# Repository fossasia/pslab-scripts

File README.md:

# PSLab

This repo is used for scripts and operators that collect data of specific sensors connected with the PSLab.

PSLab is a tiny pocket science lab that provides an array of equipment for doing science and engineering experiments. It can function like an oscilloscope, waveform generator, frequency counter, programmable voltage and current source and also as a data logger. Our website is at https://pslab.io

## The PSLab Sensor Box

For a quick start jump to the [initial setup](#initial-setup) or the [basic usage](#basic-usage) section.

In this project four different experimental setups of the [PSLab v5](https://pslab.io/wp-content/uploads/PSLab-Data-Sheet.pdf) are created, each incorporating a different sensor: one measuring [CO2](/docs/sensors.md#⬛-co2e-sensor-ccs811), one for [oxygen](/docs/sensors.md#🟦-oxygen-sensor-ao-03), one for [temperature](/docs/sensors.md#🟩-temperature-sensor-lm35), as well as one setup measuring the [light intensity in lux](/docs/sensors.md#🟨-light-intensity-sensor-gl5528).
Details for those sensor setups can be found in the [docs](/docs/sensors.md).

In addition, the following **hardware components** are connected to the PSLabs:

- A **Raspberry Pi Zero W** to store the sensor data permanently on an SD card and, at the same time, make this data available via the Raspberry Pi's WiFi module. The "Zero" is especially handy here, as it is the most lightweight Raspberry Pi version. Both, the Raspi and the PSLab are screwed on to a plexiglass panel that is slid into the box using the boxe's integrated rail system.
- A **Button** to safely shutdown the Raspberry Pi. It needs to be long pressed for at least one second in order to trigger the device's shutdown. Here, one button terminal is plugged into GPIO pin 27, while the other terminal is plugged to the ground.
- The high accuracy I²C **real time clock (RTC)** model [DS3231](https://www.analog.com/media/en/technical-documentation/data-sheets/DS3231.pdf). It contains a small battery and ensures that the device's time progresses, even if the main power source is unavailable. This RTC therefore makes timestamps in the output data possible during times, where the PSLab sensor box can not access the internet. The five pins of this Pi HAT are plugged into pins 1, 3, 5, 7 and 9 of the Raspberry Pi Zero W.
- A 3D printed, splashproof [casing](/docs/casing/README.md) with a USB c port and a lasercut shield to hold the electronics securely in place.

The following **features** are implemented on top of that:

- Each measured data point is then immediately shared via OSC as `/<item_name> <measured_value>, <unit>, <timestamp>`. Additionally it is written into the CSV file of this measurement session. The file is structured as `<timestamp>, <measured_value>, <unit>, <item_name>`.
- The devices are connected to a public WiFi Network, where they share their data as part of an IoT approach. Initially, each device opened their own WiFi Hotspot, however this was later **discontinued**, as the new requirement of accessing all devices within one common network came up.
- A [samba file sharing server](https://raspberrypi-guide.github.io/filesharing/filesharing-raspberry-pi) makes the folder "/home/foss/data" of the Raspberry Pi publicly available to all devices within the WiFi Hotspot. This also enables users to modify or delete the CSV measurement data within this folder remotely via their PC or mobile phone. The measurements are not only provided to this file sharing server in real-time, but also stored on the SD card permanently.
- The measurement it triggered automatically after startup. This is done by a custom [systemd](https://www.raspberrypi-spy.co.uk/2015/10/how-to-autorun-a-python-script-on-boot-using-systemd/) service.
- The Raspberry Pi itself is running the code from the master branch this Github repository. This makes code updates easy to distribute on all devices. All PSLab sensor boxes run the exact identical code, with the only difference being the experiment type parameter with which `init_pipe.py` is called by the systemd service.

## Accessing the Raspberry Pi

In order to modify the software, the data on the Raspberry Pi's SD card needs to be accessed.
This can either be done by plugging the SD card into a computer, accessing the Raspberry Pi via SSH, or by using the Raspi as a computer itself. In the following, the latter two methods are explained in detail.
In any case, the SD card should never be cleared fully, because this would delete the operating system and therefore stop the Raspberry Pi from working.

### Using the Raspberry Pi as an Independent Computer

Here, a monitor needs to be connected to the microHDMI slot of the Raspi. Simultaneously a mouse and a keyboard need to be linked to the inner microUSB slot via an USB hub. Make sure to perform this cabling-up before attaching the device to the electricity source.

### Accessing the Raspberry Pi via SSH

An [SSH access](https://itsfoss.com/ssh-into-raspberry/) can be more convenient, as there is no additional cabling needed.
However, to establish this connection, the Raspberry Pi needs to be in the same WiFi network as the connecting laptop. If that is not the case yet, there is no way around connecting the Raspi to a monitor first, in oder to set up this WiFi connection, as the Raspberry Pi Zero W does not have a LAN port. Also, the network specific **IP address** of the Raspberry Pi needs to be known. It can be retrieved by executing the command `ifconfig` in the Raspi's terminal while having it connected to a monitor. The IP address can then usually be found in the "wlan0" paragraph and is formatted in a "000.000.000.000" pattern.
To then establish the ssh connection, the following steps need to be executed:

1. Ensure that the PC is connected to the same WiFi Hotspot as the PSLab Sensor Box.
2. Open the SSH connection by running `ssh foss@<ip>` in the PC's terminal and entering the password `foss` when asked.
3. Now you are operating on the Raspberry Pi.

## Initial Setup

Before using the devices in an own network, a one time setup is needed.
Once this is done, for every following usage, please directly jump to the [basic usage](#basic-usage) section.

Both, the OSC messages and the CSV file, of the measurement can be retrieved via WiFi.
Currently, the devices are connected to a dummy WiFi Hotspot with the credentials `myHotspot` as the SSID and `password123` as the password.
Thus, for basic testing, one can just open a Hotspot with these details on a Phone/PC, the devices will automatically connect and the measurement data can be obtained.

However, for more extensive usage, it is obviously more convenient to connect the PSLab Sensor Boxes to the buildings usual WiFi.
For example a connection to eduroam can be established by [logging in with one's university credentials](https://www.uni-weimar.de/fileadmin/user/uni/zentrale_einrichtungen/scc/wlan/Ubuntu.pdf).
The network connection can be changed by [connecting the Raspberry Pi to a monitor](#using-the-raspberry-pi-as-an-independent-computer) and logging into the new WiFi Hotspot using the graphical user interface. Once connected, it is also possible to [set a static private IP address](https://www.tomshardware.com/how-to/static-ip-raspberry-pi) for the Raspberry Pi in this network.
This can be very useful, for example, in order to make the Raspi reliably accessible via SSH.
Please make sure that the devices can see each other in the network and disable/ reconfigure the [VLAN](https://www.techtarget.com/searchnetworking/definition/virtual-LAN), in case one is set up.

Additionally, the IP address and port of the OSC server, need to be edited according to the actual address of the OSC receiver.
This can be done by adjusting the `OSC_RECEIVER_IP` and the `OSC_RECEIVER_PORT` constants on the Raspberry Pis.
The only loophole to this, is to use a OSC server at the pre-configured IP address of `192.168.173.152`.
However, that's not always possible, depending on the available namespace of the network.

## Basic Usage

Once a power source (power bank or cord to electricity outlet) is connected to the PSLab sensor box and the device has fully booted (this **may take a minute ot two**), a new measurement is automatically started. The measurement results are now simultaneously shared via the [Open Sound Control Protocol (OSC)](https://en.wikipedia.org/wiki/Open_Sound_Control) and collected in a [CSV](https://en.wikipedia.org/wiki/Comma-separated_values) file.
To retrieve this data, please connect your own PC/Phone to the same public WiFi Hotspot, that the PSLab Sensor Box is connected to (see [initial setup](#initial-setup)).

### Accessing the CSV Measurements

The CSV measurements of each PSLab sensor box can be retrieved in real time from the file server via WiFi:

1. A detailed manual on how to connect to the devices file server for the first time can be found in the [docs](/docs/network_connection_manual.md).
2. Once connected, the PSLab will appear in the "Network Devices" section.

Access the data folder and fetch the most recent CSV measurement data file. This file can for example be opened by Excel or just a normal text editor. The current measurement file is updated automatically every few seconds, to see these real time changes, just close and reopen the file.

Analysis tasks can now be performed on these data sheets, for example by importing them into [Jupyter Notebook](https://jupyter.org/).

### Receiving the OSC Messages

The OSC messages are sent to the specified IP address upon startup. To receive those messages a OSC server like this is necessary:

```[python]
import argparse
from pythonosc.dispatcher import Dispatcher
from pythonosc import osc_server

if __name__ == "__main__":
    parser = argparse.ArgumentParser()
    parser.add_argument("--ip", default="192.168.173.152")
    parser.add_argument("--port", type=int, default=5005)
    args = parser.parse_args()

    dispatcher = Dispatcher()
    dispatcher.map("/light", print)
    dispatcher.map("/temp", print)
    dispatcher.map("/co2", print)
    dispatcher.map("/oxygen", print)

    server = osc_server.ThreadingOSCUDPServer(
        (args.ip, args.port), dispatcher)
    server.serve_forever()
```

This server uses the [python-osc](https://github.com/attwad/python-osc) package to receive and decode the messages. The package can be installed by executing `pip3 install python-osc` in the PC's terminal.
Please note that this setup only works if the IP address, specified as `OSC_RECEIVER_IP`, is identical to the IP address stated in the server scrips (in line 7 here) and corresponds to the laptops own IP address (obtainable by executing "ifconfig" in the terminal). This OSC server for example produces the following output when, at the same time, the Oxygen Sensor Box and the Light Sensor Box are sending OSC data to this IP address at port 5005:

### Example Measurement Session

When for example using the PSLab Sensor Box "Lux", changes in the environment's light intensity can be measured.
After attaching the box to a power bank and waiting for two minutes, the device starts measuring.

The running OSC server on our laptop, that is connected to the same WiFi Hotspot as the Sensor Box, then receives the following data:

```
/light 109.5234702837157 lux 21-07-2023 20:44:12
/light 108.62976013160224 lux 21-07-2023 20:44:13
/light 114.54458695414951 lux 21-07-2023 20:44:14
```

To test the sensor and observe the changes in the environment, the lights are now turned off.

This results in the following OSC messages:

```
/light 6.80740388396548 lux 21-07-2023 20:46:04
/light 7.05431189748499 lux 21-07-2023 20:46:05
/light 7.52577384043171 lux 21-07-2023 20:46:06
```

To then test the sensor at a very hight brightness, we turned the lights on again and exposed the photoresistor to a flashlight:

Thus, the OSC server receives these messages:

```
/light 1721.79974583536023 lux 21-07-2023 20:47:38
/light 1902.29013779831879 lux 21-07-2023 20:47:39
/light 1483.70672770591856 lux 21-07-2023 20:46:40
```

In an analogue way, the temperature sensor can be tested by warming it up with one's finger tips,
while the CO2 and oxygen sensors can by tested by exposing them to exhaled air.

### Ending the Session

To eventually trigger the shut down process of the Raspberry Pi, please press the attached button for one to two seconds.
After waiting 20-30 seconds, the shut down is completed, the green indication light on the Raspberry Pi goes off and the electricity source can be unplugged.
Technically, the measurement session can also be terminated by just unplugging the power source directly, however in the long term,
this technique can be harmful for the Raspberry Pi's file system.

## Debugging

As this is a hardware project, it is not unlikely that at some point in time, one of the cables or other components will cause problems. To then solve this, it is important to localize the error. Here, different levels of debugging can help, depending on the supposed location of the problem.
Basic debugging steps may be:

- Turn the Raspberry Pi off (by using the button) and on again (by plugging in a power bank).
- Make sure all cables are attached firmly. Try unplugging and reattaching them.
- Sometimes the output voltage of a laptop's USB port might vary a bit to much, try using a power bank instead.
- Make sure the lights on the PSLab are glowing. Otherwise there probably is a problem with the boxes' charging cable or the PSLab itself.
- Make sure the light on the Raspberry Pi is glowing or blinking. This indicates a successful booting of the Raspbian OS.
- Try using one PSLab Sensor Box after another, not in parallel.
- If the device does not connect to the WiFi network (for example checkable via Linux' `nmap` tool), try having the network open already during the Raspberry Pi's booting process.
- Try opening the Hotspot, that the Sensor Boxes are connected to, from another device (e.g. phone, instead of laptop).

Some more advanced debugging techniques include the following:

### Debugging Sensor Issues - On a PC

To ensure that the PSLab itself and the sensor are working properly,  the following test can be executed.
Please note that this routine is the only one that is executed on a normal (Linux)
**PC, instead of the Raspberry Pi**, in order to abstract from any Raspi specific problems.

1. Ensure that python3 is installed on your PC by running `python3 --version` in the terminal. In case there is no item found, install version 3.6 by `sudo apt-get install python3.6` and reboot your system afterwards to ensure that everything is fully loaded.
2. Install the pslab-python library on the PC by executing `pip3 install pslab`.
3. Detach the PSLab and the corresponding sensor from the Raspberry Pi by removing the
microUSB to microUSB cable between Raspi and PSLab. Instead connect the microUSB port of the PSLab to one of the PC's USB ports.
4. Download the pslab-scripts library by running `sudo git clone https://github.com/fossasia/pslab-scripts.git`.
5. Open the repository folder by executing `cd pslab-scrips`.
6. Start the execution a sensor type specific test by running `sudo python3 init_pipe.py <type>` (for example
`sudo python3 init_pipe.py oxygen`). This execution can always be stopped by hitting ctrl+c.
7. Check the fetched measurement data by accessing the file located in `/home/<user name>/data`.

### Debugging the Startup Script - On the Raspberry Pi

Often times the script itself actually works fine, but the startup manager might start it
too early, causing resource conflicts and other issues to arise.
One option to debug this, is to first make sure that the script itself works fine by running `sudo python3 /home/foss/code/init_pipe.py <type>`
on the Raspberry Pi (for example `sudo python3 init_pipe.py oxygen`) and checking the results in
`/home/foss/data`. If those results look good, but the data fetching upon startup still does not work, the error logs of the startup script can be examined by executing `journalctl -u startup.service --since yesterday` in the Raspi's terminal.

## Advanced Usage

Different software and hardware projects can be realized on this combination of PSLab and Raspberry Pi.
Some ideas for modifying the existing software are listed below.
As python3, the pslab-python library, as well as this pslab-scripts repository, are already installed on the Raspberry Pis, **no** additional installation is needed here.

### Adjusting the measurement interval

Currently a new data point is retrieved from the sensor every second. This can be changed by adjusting the value for the`MEASURING_INTERVAL`. This constant can be found in the `/home/foss/pslab-scripts/measure.py` file on the Raspberry Pi.

### Adjusting the flushing interval

The data points are flushed into the CSV file after every 10 measurements in the current implementation. To change this, the `FLUSHING_THRESHOLD` value in `/home/foss/pslab-scripts/store_data.py` can be adjusted on the Raspi.

### Accessing the continuous measurement data stream via an API

As of now, the measurement data is redirected into a CSV file and OSC messages by the pipe function. This can however be modified freely, for example by adding an additional step 
to transform and output some data into the data exporting function.
This new process can freely process the measured data points, received via `connection.recv()`.

### Fetching a software update from Github

1. Open the terminal.
2. Open the folder "pslab-scripts" by typing `cd /home/foss/pslab-scripts`.
3. Enter `git pull` in the terminal to fetch the new changes in software.

### Changing the sensor type

By adjusting the experiment type parameter in the systemd service "startup.service", the supported sensor type of this specific PSLab sensor box can be changed easily:

1. Open a terminal.
2. Type `sudo nano /lib/systemd/system/startup.service`.
3. The "startup.service" file is now opened in a simple text editor. Here, you can adjust the experiment type parameter, e.g. from "light" to "co2", in case the PSLab sensor box for light shall now be used with a CO2 sensor. Besides "light" and "co2", also "oxygen" and "temp", are supported as parameters here.
4. Save the changes by pressing ctrl+o. Exit the editor by pressing ctrl+x.
5. The changes take effect once the device is rebooted. This can for example be done by executing `sudo reboot`.

## Repository Structure

```
📦pslab-scripts
 ┣ 📂docs                               # Supplementary material
 ┃ ┣ 📂ao-03_amplifier_circuit_design  # KiCad project files of the custom circuit board for the AO-03 sensor
 ┃ ┃ ┗ 📜...
 ┃ ┣ 📂casing                          # Information about the 3d printed casing, as well as the lasercut shield
 ┃ ┃ ┣ 📜README.md
 ┃ ┃ ┗ 📜...
 ┃ ┣ 📂images
 ┃ ┃ ┗ 📜...
 ┃ ┣ 📂logos                           # Sticker designs for the boxes (made with Inkscape)
 ┃ ┃ ┗ 📜...
 ┃ ┣ 📜network_connection_manual.md    # Manual on how to connect a device to the PSLab's file server
 ┃ ┣ 📜presentation_may28.pdf
 ┃ ┣ 📜sensors.md                      # Detailed descriptions of all four sensor setups
 ┃ ┗ 📜testing_manual.md               # Detailed manual on how to test the devices
 ┣ 📂sensors                            # Contains a specific run script for every sensor
 ┃ ┣ 📜ao03_oxygen.py
 ┃ ┣ 📜ccs811_co2.py
 ┃ ┣ 📜driver_ccs811.py                # Custom driver for the CCS811 sensor
 ┃ ┣ 📜gl5528_light.py
 ┃ ┗ 📜lm35_temp.py
 ┣ 📜export_data.py                     # Sharing the measurements via OSC and CSV
 ┣ 📜init_pipe.py                       # Main project file
 ┣ 📜measure.py
 ┗ 📜shutdown.py                        # Script for the button logic
```

## Buy

* You can get a Pocket Science Lab device from the [FOSSASIA Shop](https://fossasia.com).
* More resellers are listed on the [PSLab website](https://pslab.io/shop/).

## Communication

* The PSLab [chat channel is on Gitter](https://gitter.im/fossasia/pslab).
* Please also join us on the [PSLab Mailing List](https://groups.google.com/forum/#!forum/pslab-fossasia).

## Site

The website is hosted on [pslab.io](http://pslab.io).

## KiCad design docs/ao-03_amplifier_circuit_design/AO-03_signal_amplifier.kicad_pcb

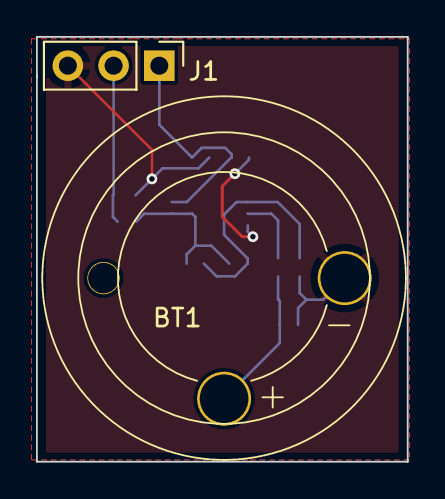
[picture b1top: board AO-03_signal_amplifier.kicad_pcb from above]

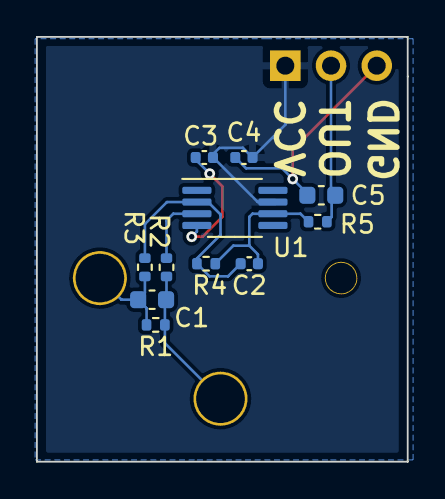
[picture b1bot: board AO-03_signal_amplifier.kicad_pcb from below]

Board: 2 copper layers, 20.6 x 23.6 mm, 13 parts (11 on the bottom side), 7 nets.

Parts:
BT1: AO3(Oxygen sensor); AO-03
C1: 4.7u; C_0603_1608Metric
C2, C3: 10n; C_0402_1005Metric
C4: 100n; C_0402_1005Metric
C5: 10u; C_0603_1608Metric
J1: Conn_01x03; PinHeader_1x03_P2.54mm_Vertical
R1, R5: 100; R_0402_1005Metric
R2, R3: 10k; R_0402_1005Metric
R4: 400k; R_0402_1005Metric
U1: AD8551ARM; MSOP-8_3x3mm_P0.65mm

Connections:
/OUT: C5.1, J1.2, R5.2
GND: BT1.2 (-), C1.2, C3.2, C4.2, C5.2, J1.3, R1.1, R3.1, U1.4 (V-)
unnamed: BT1.1 (+), C1.1, R1.2, R2.1
unnamed: C2.1, R3.2, R4.1, U1.2 (-)
unnamed: C2.2, R4.2, R5.1, U1.6
unnamed: R2.2, U1.3 (+)
VCC: C3.1, C4.1, J1.1, U1.7 (V+)

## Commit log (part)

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2015-06-25 Create gh-pages branch via GitHub
2016-07-02 Create CNAME
2016-10-31 changes for new site
2016-10-31 Adding New Site
2016-11-01 Add contributers info
2016-11-01 Add contributers
2016-11-11 colors
2016-11-11 more color changes
2016-11-11 reset
2016-11-11 redish
2016-12-12 CDNs added and some error
2016-12-12 CDNs added
2016-12-12 Add CDN
    Added CDN and removed /vendor. Page load 1.5x faster than previous(as oer chrome network throttle at 50KBps speed). Fixes #9.
2016-12-14 Site rendering issue fixed for developer page and Added Favicon
    Added Favicon
2016-12-15 Centered the navbar
2016-12-16 Centered the navbar.
2016-12-17 Impored the footer (#19)
2016-12-18 Added jQuery Smooth Scroll
    Added jQuery's smooth scrolling to make the navigation links in the
    index.html look more professional and elegant.
2016-12-19 Adding sticky navbar
2016-12-19 Added labs dropdown in navigation bar
2016-12-19 Improving and sorting navbar
2016-12-21 Adding Developers section to the main page
2016-12-22 dropdown expands on scroll over
2016-12-22 Added Labs dropdown
2016-12-23 Added fossasia logo to developers.html navbar
2016-12-23 Adding improvements to the navbar
2016-12-23 fixed issues
2016-12-24 fixed text mixing / transparent navbar issue
    Modified the the favicon so that it looks nice on dark as well as light backgrounds
2016-12-24 Fixed the issues #38 and #39
2016-12-25 issue #39 have fixed
    fixed the issue #39 added missed photo of mentor, fixed links and made
    text readable in the mentor/developer section and made footer section
    more user-friendly
2016-12-25 added svg logo
2016-12-25 issue #39 have fixed and added svg logo
    fixed the issue #39 added missed photo of mentor, fixed links and made
    text readable in the mentor/developer section and made footer section
    more user-friendly
    added svg logo
2016-12-25 decreased the size of logo
2016-12-25 issue #39 have fixed with svg logo
    fixed the issue #39 added missed photo of mentor, fixed links and made
    text readable in the mentor/developer section and made footer section
    more user-friendly
2016-12-25 Revert "issue #39 have fixed with svg logo"
2016-12-25 Fixed the text scroling mixing
2016-12-27 links act in same way and use same colors
2016-12-27 Links act in the same way and use the same colors
2016-12-27 Improved and Enhanced Footer
    The footer wasn't nice-looking, it wasn't responsive, the code wasn't
    written well and it wasn't clean, no indentation and misuse of
    attributes and several other things.
    I fixed everything, made it responsive, somehow improved and enhanced
    the design and made it look more professional!
    Solving issue #39
2016-12-27 Merge remote-tracking branch 'refs/remotes/fossasia/gh-pages' into gh-pages
    # Conflicts:
    # css/custom.css
    # index.html
2016-12-27 Improved and Enhanced Footer
    The footer wasn't nice-looking, it wasn't responsive, the code wasn't
    written well and it wasn't clean, no indentation and misuse of
    attributes and several other things.
    I fixed everything, made it responsive, somehow improved and enhanced
    the design and made it look more professional!
    Solving issue #39
2016-12-28 Made some amendments
    Aligned Contact Section to the Left
    Made Social Icons Circular
2016-12-28 Fixed nav bar on scroll bold and color remains black
2017-01-01 Improved top menu bar and centered devs' images
2017-01-07 Fixes #56: The down arrow is not consistent in the top nav bar
2017-01-11 Unified links and made onscroll of nav start at first scroll
    Unified links and made onscroll of nav start at first scroll.
    Closes #24 and #45
2017-01-12 Menu bold on scroll over
2017-04-17 links
2017-04-17 added mailing list and minor fix
2017-04-18 description
2017-04-18 mentors
2017-04-21 spelling
2017-08-19 added privacy_policy.html in repo and linked it
2017-08-21 added header and footer to privacy_policy.html
    unanchored bar line in footer
    modified top bar of privacy policy page
    revert changes in top and link main page sections
2017-08-21 renamed privacy_policy.html to privacy.html
2017-08-22 Fixed #64 added privacy_policy.html in repo and linked it (#65)
    * added privacy_policy.html in repo and linked it
    * added header and footer to privacy_policy.html
    unanchored bar line in footer
    modified top bar of privacy policy page
    revert changes in top and link main page sections
    * renamed privacy_policy.html to privacy.html
2017-09-06 Fixes issue #59 now items does not move on sliding
2017-09-07 fixes issue #66 now nav item do not shifts to left on hover
2017-09-08 Added mentors: Victoria Bondarchuk, Wan Leung Wong
2017-09-08 Fixes issue #59 now items does not move on sliding (#66)
    * Fixes issue #59 now items does not move on sliding
    * fixes issue #66 now nav item do not shifts to left on hover
2017-10-14 Added Padmal to team
2017-10-15 added vivek in dev section
2017-10-15 Adds Akarshan to the team
2017-10-15 Adds Asitava to PSLab team
2017-10-17 makes suggested changes
2017-10-19 Added Darwin Gosal in the mentors #63
2017-10-19 Added Darwin Goswal And Mitch Altman
2017-10-19 uploaded to wrong directory
2017-10-19 uploding image again
2017-10-19 Uploaded in wrong directory
2017-10-19 Again Uploading
2017-10-19 Added Mitch Altman in the Mentors #63
2017-10-19 Referenced image of Darwin Gosal
2017-10-19 Added some padding for mobile devices
2017-10-19 Added Padmal to team (#68)
2017-10-19 Adds Akarshan to the PSLab team (#71)
    * Adds Akarshan to the team
    * makes suggested changes
2017-10-22 Added some padding for better view in mobile devices
2017-10-23 done changes
    Fixed some id's and white spaces and links
2017-10-23 reverted changes
    reverted changes in custom.css
2017-10-23 Adds Asitava to PSLab team (#69)
2017-10-23 Changed fa icons and the label font-family in footer section
2017-10-24 Changed fa icons and the label font-family in footer section (#75)
2017-10-27 Asitavas image was not showing up on site!
2017-10-28 Asitavas image was not showing up on site! (#78)
2017-11-05 Back to top button
2017-11-18 fix the issue for #83
2017-12-02 Added all mentors as requested; Issue#63 completely fixed
2017-12-03 Made the image sizes uniform; Also replaced some images
2017-12-03 Link to csparkresearch.in was not working
2017-12-03 Fixes #63 (#85)
    * Added all mentors as requested; Issue#63 completely fixed
    * Made the image sizes uniform; Also replaced some images
2017-12-03 Link to csparkresearch.in was not working (#86)
2017-12-21 Added 404 and 500 Pages
2017-12-27 Added 404 and 500 Pages (#88)
2018-01-04 Create index.html with font awesome
2018-01-23 ideas
2018-03-08 Icons from font awesome are added in the navbar
2018-05-12 Fixes #93 : Converted insecure links in the codebase
2018-05-22 Added uniform spacing to the page along with spacing the numbering bullets
2018-05-25 Fixed preformatted texts
2018-05-29 Fix the styling of FOSSASIA on page top left.
    When website is resized, styling of word FOSSASIA on
    page top left is broken, especially when the navbar toggles.
    This is happening due to the absence any listener for width
    change event. Submitting a fix for it.
    Fixes #95.
2018-06-04 Added lazy load functionality
    Removed extra files
    Refracted the lazy-load.min file to remove extra spaces
2018-06-07 Fixes #102 : Added contribution best practices and description in readme
2018-06-08 Fixes #102 : Added contribution best practices and description in readme (#106)
2018-06-08 Fixed preformatted texts (#101)
2018-06-08 Icons from font awesome are added in the navbar (#91)
2018-06-08 Pslab fossasia (#84)
    * fix the issue for #83
    * fix the issue for #83
2018-06-08 Fix the styling of FOSSASIA on page top left. (#96)
    When website is resized, styling of word FOSSASIA on
    page top left is broken, especially when the navbar toggles.
    This is happening due to the absence any listener for width
    change event. Submitting a fix for it.
    Fixes #95.
2018-06-08 Fix issue now item does not move on scroll down
2018-06-10 isssue #59 resolved, commmit deleted
2018-06-23 Update of PSLab schematics link in the menu
2018-06-23 Update of PSLab schematics link in the menu (#108)
2018-07-13 navbar logo made inline
2018-07-13 Update CNAME
2018-09-16 index.html:Social media icons
    In the website, social media icons are not working so I did some changes in the index.html and fix this
2018-09-16 index.html:Social media icons (#114)
    In the website, social media icons are not working so I did some changes in the index.html and fix this
2018-10-03 fixes #115
2018-10-08 fix(index): Fixed desktop app URL
2018-10-08 fixes #115 and also de-indented the code by 2 spaces
2018-10-10 fix(index): Fixed desktop app URL (#119)
2018-10-10 Inserted new lines and fixes #115
2018-10-13 updated PSLab schematics
2018-10-13 updated PSLab schematics (#121)
2018-10-20 Added HTTP 504
2018-12-17 Update Profile Lorenz Gerber
2018-12-18 Aligned contact us links
2019-04-01 Fix Twitter link on homepage (fixes #146)
2019-04-02 Fix Twitter link on homepage (fixes #146) (#147)
2019-05-04 Updated meta description to Privacy Policy
2019-05-05 Updated meta description and title
2019-11-01 Bump jquery from 1.12.4 to 3.4.1
    Bumps [jquery](https://github.com/jquery/jquery) from 1.12.4 to 3.4.1.
    - [Release notes](https://github.com/jquery/jquery/releases)
    - [Commits](https://github.com/jquery/jquery/compare/1.12.4...3.4.1)
2019-12-11 Update: add contribution and license in the README file
2019-12-11 Update: add license in the README file
2019-12-22 Added some more social accounts
2020-04-29 Bump jquery from 1.12.4 to 3.5.0
    Bumps [jquery](https://github.com/jquery/jquery) from 1.12.4 to 3.5.0.
    - [Release notes](https://github.com/jquery/jquery/releases)
    - [Commits](https://github.com/jquery/jquery/compare/1.12.4...3.5.0)
2020-10-07 Update LICENSE
2020-10-28 create website chatbot
    create website chatbot for interact the website users and end user easy to access the website
    solve the website user problem more efficiently.
2020-10-29 Updated index.html and changed it for better view.
    Changed and updated the comments so to make it more readable. Also changed the mentors and developers name in Italics for better view.
2020-10-29 cleanup
2023-05-18 add general raspi code to execute measurements
2023-05-18 add analoge oxygen measurement
2023-05-18 add analoge lux measurement
2023-05-18 add device logos
2023-05-19 fix: renaming the sensor files to lower case
2023-05-19 fix: debugging the shutdown code
2023-05-19 add support for L35 temperature sensor
2023-05-19 Add script for CCS811 eCO2 and eTVOC sensor
2023-05-19 Add project document for AO-03 oxygen sensor
2023-05-19 fix: allowing CO2 sensor to fail once
2023-05-19 fix: remove console output
2023-05-21 add first version of the documentation
2023-05-21 update documentation images
2023-05-21 updating the lower level readmes
2023-05-21 fix markdown subscript
2023-05-21 fix: using different subscript
2023-05-22 updating readme
2023-05-23 reformatting the readme
2023-05-26 add images for sensor connections
2023-05-26 fix image captions
2023-05-26 rearranging image descriptions
2023-05-27 removing broken links
2023-06-12 add testing manual for prototype version
2023-06-12 fix: adding and updating links
2023-06-16 re-calibrating the light sensor
2023-06-16 adding osc support
2023-06-16 debugging "unknown args" error
2023-06-16 removed pickle bug
2023-06-18 adding documentation for the osc feature
2023-06-20 add pip3 commands into the docs
2023-07-16 parallelizing osc sharing and csv saving
2023-07-19 updating docs
2023-07-19 fixing some markdown design issues
2023-07-19 add option for using "all" sensors
2023-07-19 recalibrating new oxygen sensors
2023-07-19 fixing ccs811 driver bugs
2023-07-20 add sensor color codes
2023-07-21 recalibrating oxygen sensor
2023-07-21 updating ssh setup manual
2023-07-24 add casing files
2023-07-24 add casing documentation
2023-07-24 update images
2023-07-24 updating connection manual
2023-07-24 updating sensor connection documentation
2023-07-24 updating the readme
2023-07-24 cropping images
